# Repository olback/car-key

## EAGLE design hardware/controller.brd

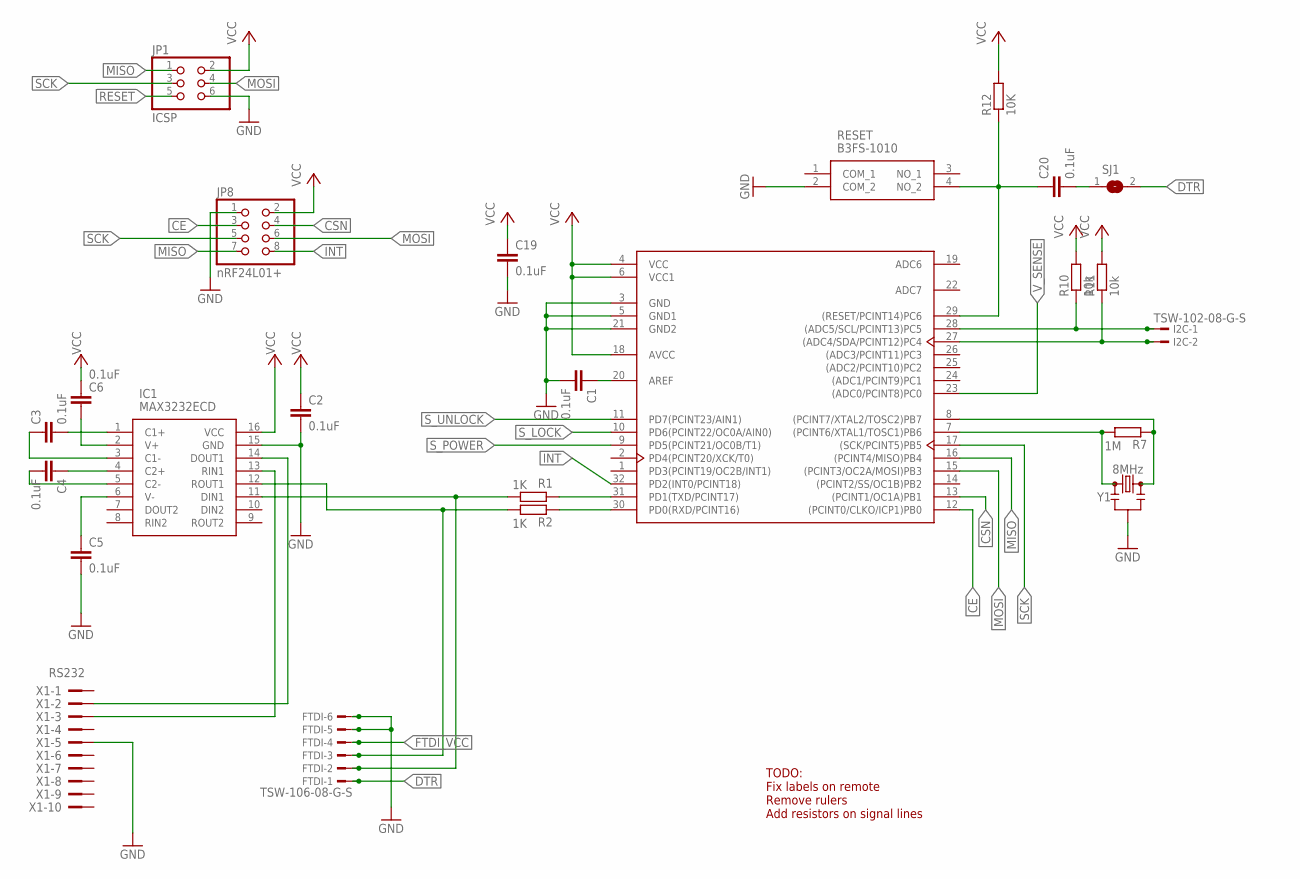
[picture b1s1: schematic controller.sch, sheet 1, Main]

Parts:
C1, C2, C3, C4, C5, C6, C19, C20: 0.1uF; C0805
FTDI: TSW-106-08-G-S; TSW-106-XX-G-S
I2C: TSW-102-08-G-S; TSW-102-XX-G-S
IC1: MAX3232ECD; SOIC127P600X175-16N
JP1: ICSP; 2X03
JP8: nRF24L01+; 2X04
R1, R2: 1K; R0805
R7: 1M; R0805
R10, R11: 10k; R0805
R12: 10K; R0805
RESET: B3FS-1010; B3FS-1000P
SJ1: SJ
U2: ATMEGA328P-AU; TQFP-32
X1: RS232; PAK100/2500-10
Y1: 8MHz; RESONATOR-SMD-3.2X1.3

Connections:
CE: JP8.3, U2.12 ((PCINT0/CLKO/ICP1)PB0); also elsewhere on the board
CSN: JP8.4, U2.13 ((PCINT1/OC1A)PB1); also elsewhere on the board
DTR: FTDI.1, SJ1.2
FTDI_VCC: FTDI.4; also elsewhere on the board
GND: C1.2, C2.2, C5.2, C19.2, FTDI.5, FTDI.6, IC1.15 (GND), JP1.6, JP8.1, RESET.2 (COM_2), U2.3 (GND), U2.5 (GND1), U2.21 (GND2), X1.5, Y1.2; also elsewhere on the board
INT: JP8.8, U2.32 (PD2(INT0/PCINT18)); also elsewhere on the board
MISO: JP1.1, JP8.7, U2.16 ((PCINT4/MISO)PB4); also elsewhere on the board
MOSI: JP1.4, JP8.6, U2.15 ((PCINT3/OC2A/MOSI)PB3); also elsewhere on the board
unnamed: C1.1, U2.20 (AREF)
unnamed: R7.2, U2.7 ((PCINT6/XTAL1/TOSC1)PB6), Y1.1
unnamed: R7.1, U2.8 ((PCINT7/XTAL2/TOSC2)PB7), Y1.3
unnamed: R1.1, U2.31 (PD1(TXD/PCINT17))
unnamed: R2.1, U2.30 (PD0(RXD/PCINT16))
unnamed: C5.1, IC1.6 (V-)
unnamed: C3.2, IC1.1 (C1+)
unnamed: C4.2, IC1.5 (C2-)
unnamed: C3.1, IC1.3 (C1-)
unnamed: C4.1, IC1.4 (C2+)
unnamed: C6.1, IC1.2 (V+)
unnamed: IC1.13 (RIN1), X1.3
unnamed: IC1.14 (DOUT1), X1.2
unnamed: C20.2, SJ1.1
RESET: C20.1, JP1.5, R12.1, RESET.4 (NO_2), U2.29 ((RESET/PCINT14)PC6)
RX-I: FTDI.3, IC1.12 (ROUT1), R2.2
SCK: JP1.3, JP8.5, U2.17 ((SCK/PCINT5)PB5); also elsewhere on the board
SCL: I2C.1, R10.1, U2.28 ((ADC5/SCL/PCINT13)PC5)
SDA: I2C.2, R11.1, U2.27 ((ADC4/SDA/PCINT12)PC4)
S_LOCK: U2.10 (PD6(PCINT22/OC0A/AIN0)); also elsewhere on the board
S_POWER: U2.9 (PD5(PCINT21/OC0B/T1)); also elsewhere on the board
S_UNLOCK: U2.11 (PD7(PCINT23/AIN1)); also elsewhere on the board
TX-O: FTDI.2, IC1.11 (DIN1), R1.2
VCC: C2.1, C6.2, C19.1, IC1.16 (VCC), JP1.2, JP8.2, R10.2, R11.2, R12.2, U2.4 (VCC), U2.6 (VCC1), U2.18 (AVCC); also elsewhere on the board
V_SENSE: U2.23 ((ADC0/PCINT8)PC0); also elsewhere on the board

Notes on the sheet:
TODO: Fix labels on remote Remove rulers Add resistors on signal lines

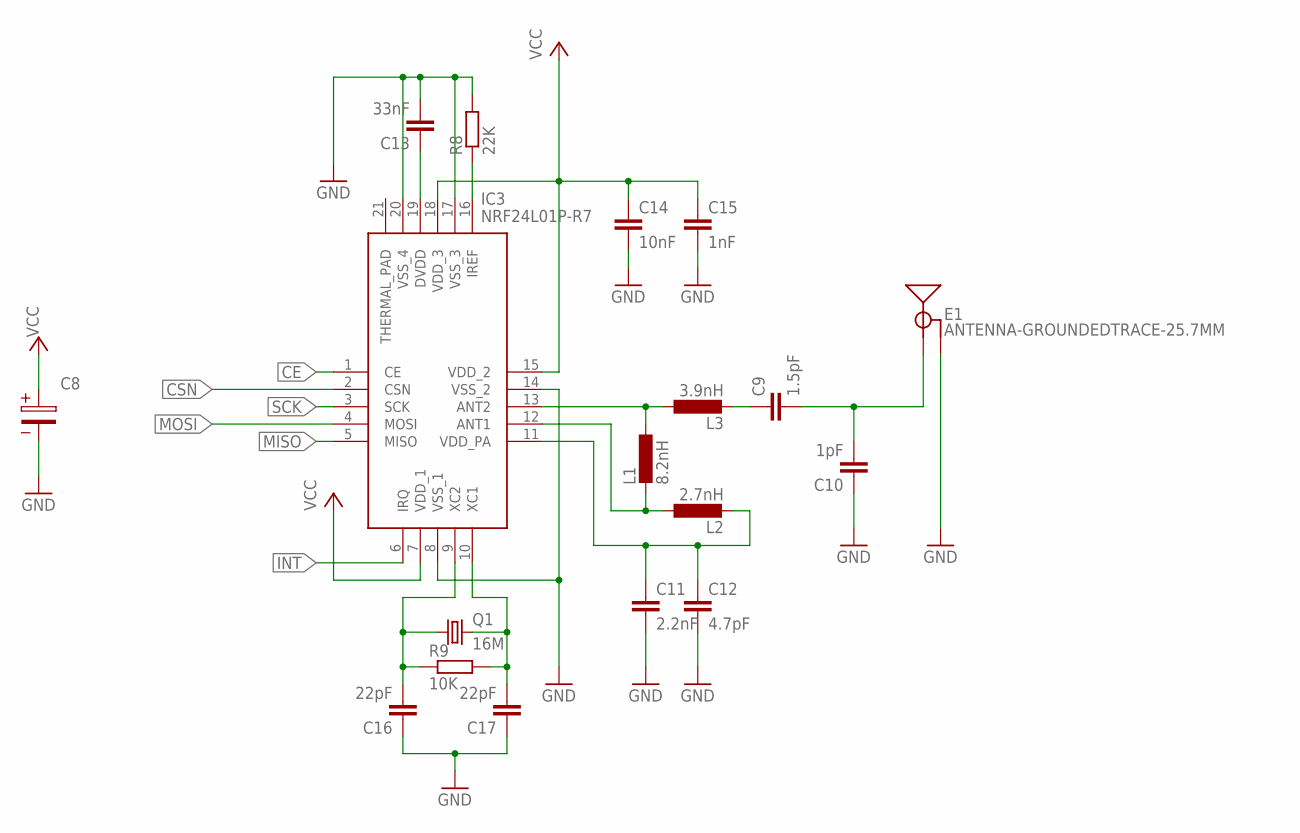
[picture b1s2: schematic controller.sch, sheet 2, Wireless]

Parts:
C8: WCAP-ASLI_8X6,5_865080149011; 4.2X1.9X2.8(BXCXA)
C9: 1.5pF; C0805
C10: 1pF; C0805
C11: 2.2nF; C0805
C12: 4.7pF; C0805
C13: 33nF; C0805
C14: 10nF; C0805
C15: 1nF; C0805
C16, C17: 22pF; C0805
E1: ANTENNA-GROUNDEDTRACE-25.7MM; TRACE_ANTENNA_2.4GHZ_25.7MM
IC3: NRF24L01P-R7; QFN50P400X400X95-21N
L1: 8.2nH; L2012C
L2: 2.7nH; L2012C
L3: 3.9nH; L2012C
Q1: 16M; HC49/S
R8: 22K; R0805
R9: 10K; R0805

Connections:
CE: IC3.1 (CE); also elsewhere on the board
CSN: IC3.2 (CSN); also elsewhere on the board
GND: C8.2, C10.1, C11.2, C12.2, C13.2, C14.2, C15.2, C16.1, C17.1, E1.GND, E1.GND2 (GND), IC3.8 (VSS_1), IC3.14 (VSS_2), IC3.17 (VSS_3), IC3.20 (VSS_4), R8.2; also elsewhere on the board
INT: IC3.6 (IRQ); also elsewhere on the board
MISO: IC3.5 (MISO); also elsewhere on the board
MOSI: IC3.4 (MOSI); also elsewhere on the board
unnamed: IC3.13 (ANT2), L1.1, L3.1
unnamed: IC3.12 (ANT1), L1.2, L2.1
unnamed: C11.1, C12.1, IC3.11 (VDD_PA), L2.2
unnamed: C9.1, L3.2
unnamed: C9.2, C10.2, E1.ANT (SIGNAL)
unnamed: C13.1, IC3.19 (DVDD)
unnamed: C16.2, IC3.9 (XC2), Q1.1, R9.1
unnamed: C17.2, IC3.10 (XC1), Q1.2, R9.2
unnamed: IC3.16 (IREF), R8.1
SCK: IC3.3 (SCK); also elsewhere on the board
VCC: C8.1, C14.1, C15.1, IC3.7 (VDD_1), IC3.15 (VDD_2), IC3.18 (VDD_3); also elsewhere on the board

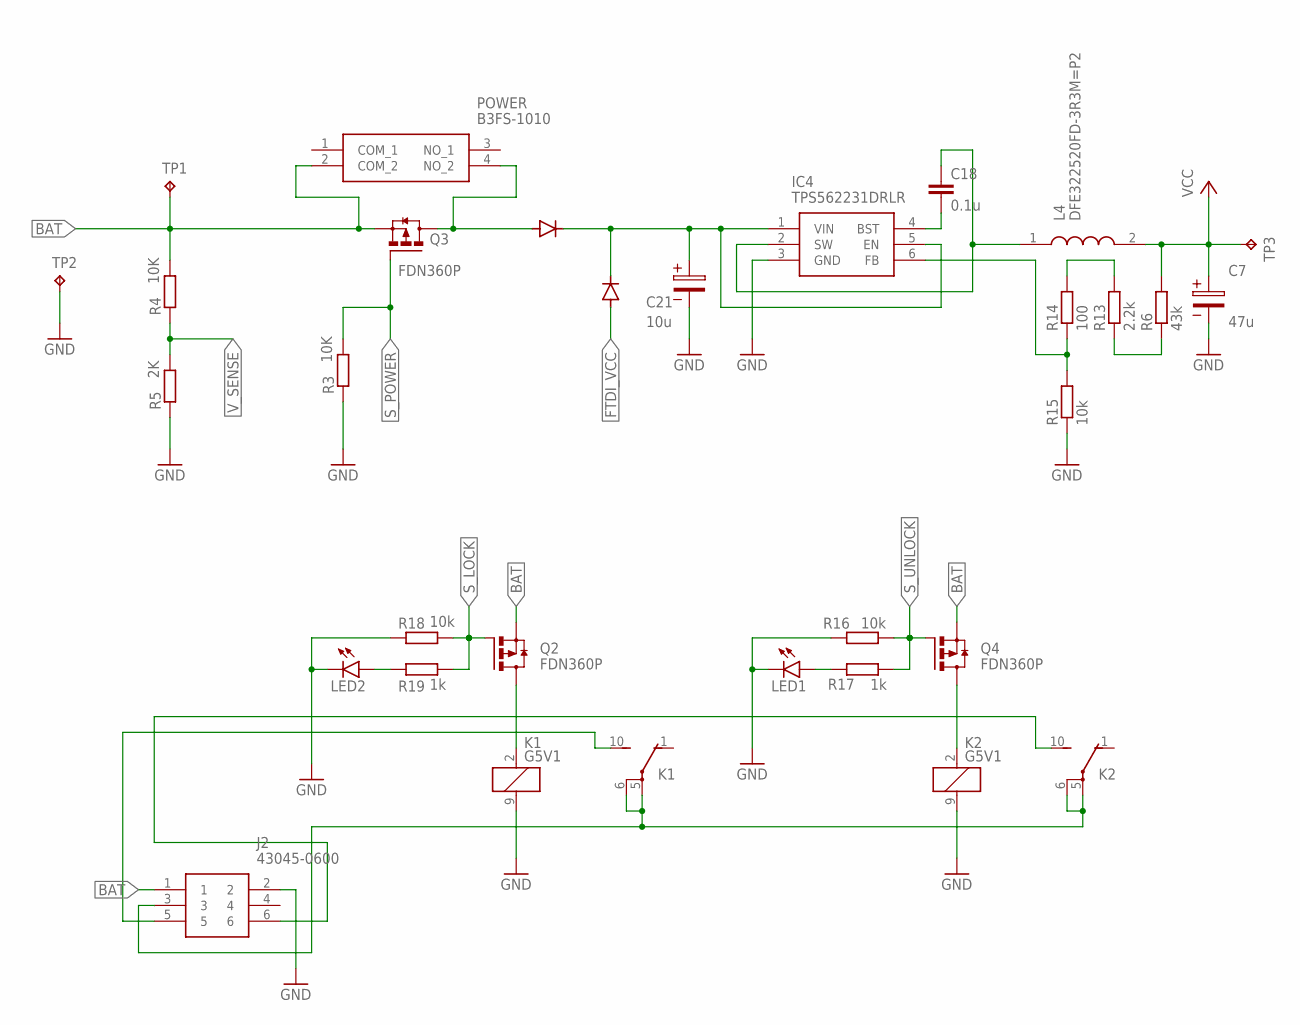
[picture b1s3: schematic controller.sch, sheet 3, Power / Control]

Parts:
C7: 47u; 2.6X1.6X1(BXCXA)
C18: 0.1u; C0805
C21: 10u; 2.6X1.6X1(BXCXA)
D1, D2: DIODE-SOD123; SOD123
IC4: TPS562231DRLR; SOTFL50P160X60-6N
J2: 43045-0600
K1, K2: G5V1
L4: DFE322520FD-3R3M=P2; INDC3225X200N
LED1, LED2: LEDCHIPLED_0805; CHIPLED_0805
POWER: B3FS-1010; B3FS-1000P
Q2, Q3, Q4: FDN360P; SUPER-SOT3
R3, R4: 10K; R0805
R5: 2K; R0805
R6: 43k; R0805
R13: 2.2k; R0805
R14: 100; R0805
R15, R16, R18: 10k; R0805
R17, R19: 1k; R0805
TP1, TP2, TP3: TPB1,27; B1,27

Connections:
BAT: J2.1, POWER.2 (COM_2), Q2.2 (S), Q3.2 (S), Q4.2 (S), R4.2, TP1.TP
E_LOCK: J2.5, K1.10 (S)
E_UNLOCK: J2.6, K2.10 (S)
FTDI_VCC: D1.A; also elsewhere on the board
GND: C7.2, C21.2, IC4.3 (GND), J2.2, K1.9 (2), K2.9 (2), LED1.C, LED2.C, R3.1, R5.1, R15.1, R16.2, R18.1, TP2.TP; also elsewhere on the board
unnamed: C18.1, IC4.2 (SW), L4.1
unnamed: C18.2, IC4.4 (BST)
unnamed: R13.2, R14.2
unnamed: C21.1, D1.C, D2.C, IC4.1 (VIN), IC4.5 (EN)
unnamed: J2.3, K1.5, K1.6, K2.5, K2.6
unnamed: R6.1, R13.1
unnamed: IC4.6 (FB), R14.1, R15.2
unnamed: D2.A, POWER.4 (NO_2), Q3.3 (D)
unnamed: K1.2 (1), Q2.3 (D)
unnamed: K2.2 (1), Q4.3 (D)
unnamed: LED1.A, R17.2
unnamed: LED2.A, R19.1
S_LOCK: Q2.1 (G), R18.2, R19.2; also elsewhere on the board
S_POWER: Q3.1 (G), R3.2; also elsewhere on the board
S_UNLOCK: Q4.1 (G), R16.1, R17.1; also elsewhere on the board
VCC: C7.1, L4.2, R6.2, TP3.TP; also elsewhere on the board
V_SENSE: R4.1, R5.2; also elsewhere on the board

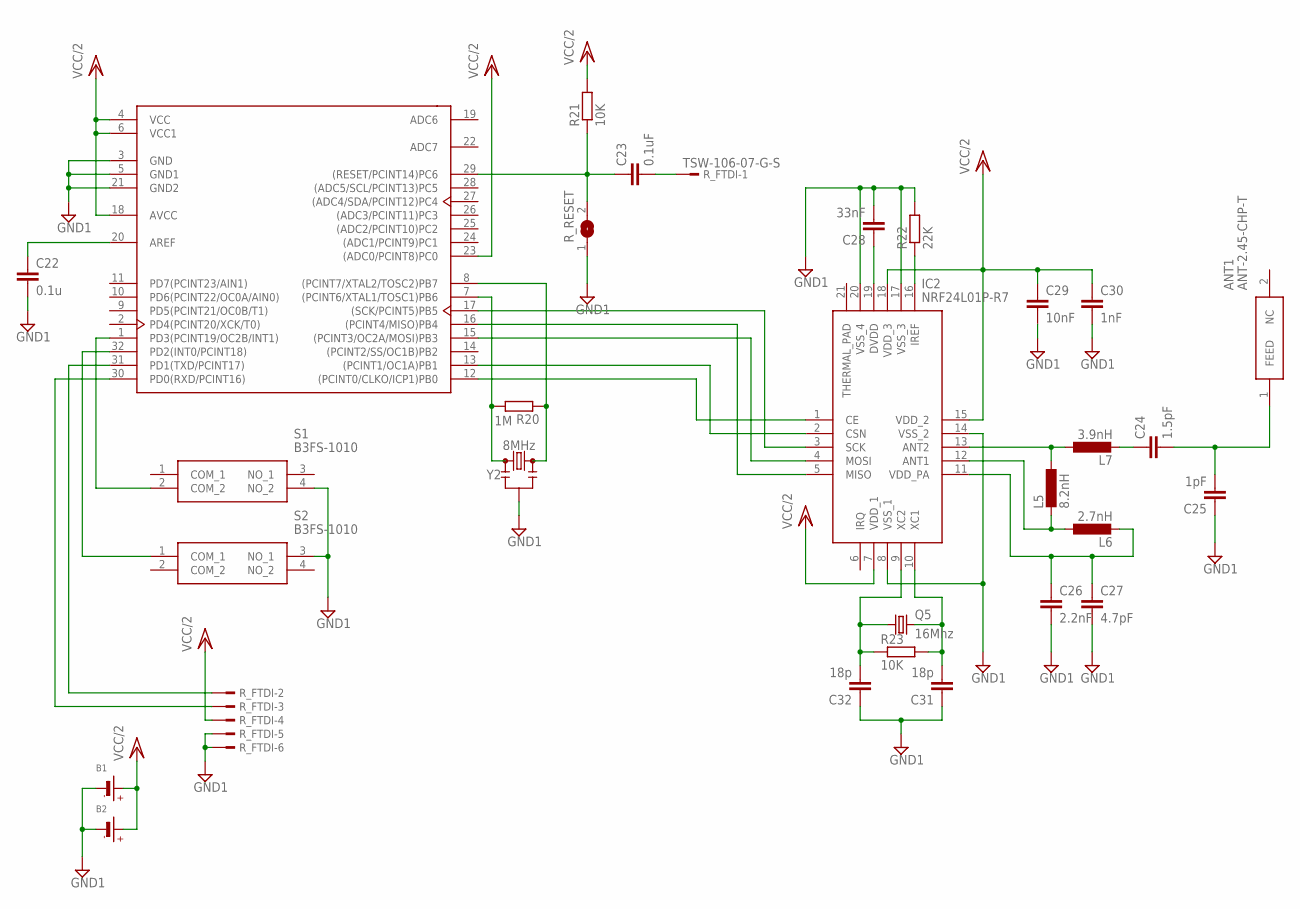
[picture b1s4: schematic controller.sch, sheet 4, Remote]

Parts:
ANT1: ANT-2.45-CHP-T
B1, B2: BATTERYCR2032_BAT-HLD-001; CR2032_SMT_BAT-HLD-001
C22: 0.1u; C0805
C23: 0.1uF; C0805
C24: 1.5pF; C0805
C25: 1pF; C0805
C26: 2.2nF; C0805
C27: 4.7pF; C0805
C28: 33nF; C0805
C29: 10nF; C0805
C30: 1nF; C0805
C31, C32: 18p; C0805
IC2: NRF24L01P-R7; QFN50P400X400X95-21N
L5: 8.2nH; L2012C
L6: 2.7nH; L2012C
L7: 3.9nH; L2012C
Q5: 16Mhz; HC49UP
R20: 1M; R0805
R21, R23: 10K; R0805
R22: 22K; R0805
R_FTDI: TSW-106-07-G-S; TSW-106-XX-G-S
R_RESET: SJ
S1, S2: B3FS-1010; B3FS-1000P
U1: ATMEGA328P-AU; TQFP-32
Y2: 8MHz; RESONATOR-SMD-3.2X1.3

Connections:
GND1: B1.-, B2.-, C22.2, C25.1, C26.2, C27.2, C28.2, C29.2, C30.2, C31.1, C32.1, IC2.8 (VSS_1), IC2.14 (VSS_2), IC2.17 (VSS_3), IC2.20 (VSS_4), R22.2, R_FTDI.5, R_FTDI.6, R_RESET.1, S1.4 (NO_2), S2.3 (NO_1), U1.3 (GND), U1.5 (GND1), U1.21 (GND2), Y2.2
unnamed: R20.2, U1.7 ((PCINT6/XTAL1/TOSC1)PB6), Y2.1
unnamed: R20.1, U1.8 ((PCINT7/XTAL2/TOSC2)PB7), Y2.3
unnamed: C22.1, U1.20 (AREF)
unnamed: S1.2 (COM_2), U1.1 (PD3(PCINT19/OC2B/INT1))
unnamed: S2.1 (COM_1), U1.32 (PD2(INT0/PCINT18))
unnamed: C23.2, R_FTDI.1
unnamed: C23.1, R21.1, R_RESET.2, U1.29 ((RESET/PCINT14)PC6)
unnamed: IC2.13 (ANT2), L5.1, L7.1
unnamed: R_FTDI.2, U1.31 (PD1(TXD/PCINT17))
unnamed: R_FTDI.3, U1.30 (PD0(RXD/PCINT16))
unnamed: IC2.12 (ANT1), L5.2, L6.1
unnamed: C26.1, C27.1, IC2.11 (VDD_PA), L6.2
unnamed: C24.1, L7.2
unnamed: ANT1.1 (FEED), C24.2, C25.2
unnamed: C32.2, IC2.9 (XC2), Q5.1, R23.1
unnamed: C31.2, IC2.10 (XC1), Q5.2, R23.2
unnamed: IC2.16 (IREF), R22.1
unnamed: C28.1, IC2.19 (DVDD)
unnamed: IC2.3 (SCK), U1.17 ((SCK/PCINT5)PB5)
unnamed: IC2.5 (MISO), U1.16 ((PCINT4/MISO)PB4)
unnamed: IC2.4 (MOSI), U1.15 ((PCINT3/OC2A/MOSI)PB3)
unnamed: IC2.2 (CSN), U1.13 ((PCINT1/OC1A)PB1)
unnamed: IC2.1 (CE), U1.12 ((PCINT0/CLKO/ICP1)PB0)
VCC/2: B1.+$1 (+), B1.+$2 (+), B2.+$1 (+), B2.+$2 (+), C29.1, C30.1, IC2.7 (VDD_1), IC2.15 (VDD_2), IC2.18 (VDD_3), R21.2, R_FTDI.4, U1.4 (VCC), U1.6 (VCC1), U1.18 (AVCC), U1.23 ((ADC0/PCINT8)PC0)

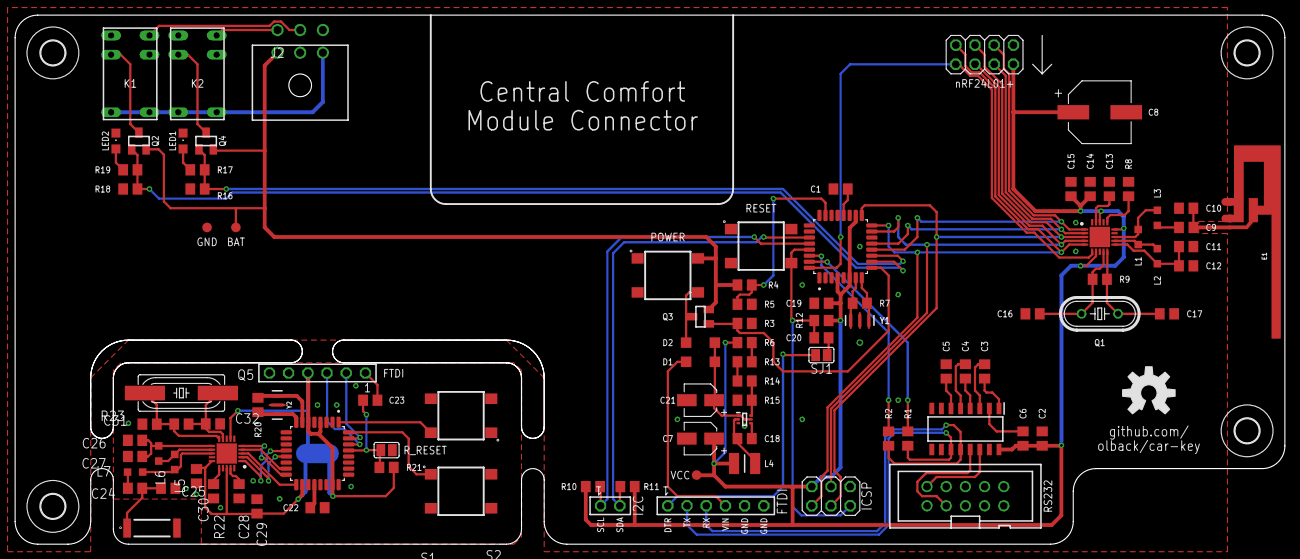
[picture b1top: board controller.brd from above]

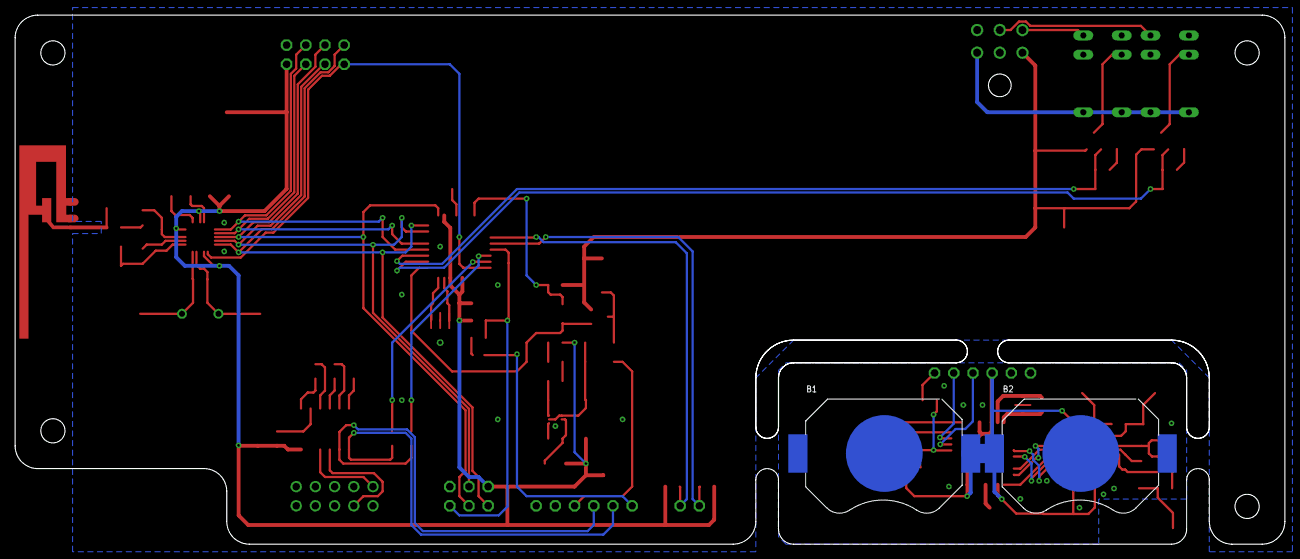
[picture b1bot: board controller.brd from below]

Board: 2 copper layers, 168.0 x 70.0 mm, 106 parts (2 on the bottom side), 82 nets.

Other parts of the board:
U$1, U$2, U$3, U$4: 3,2
U$5: OSHW-LOGO-L

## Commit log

2019-10-28 Major additions
2019-10-30 progress
2019-11-05 move psu, labels
2019-11-07 restructure + initial software drafts
2019-11-07 added base class header plus some
2019-11-09 lots of stuff
2019-11-10 start remote
2019-11-10 use 3x2 instead of 5x1
2019-11-10 move
2019-11-12 added some test stuff
2019-11-17 remote
2019-11-19 test stuff
2019-11-20 dunno

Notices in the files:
parts and their libraries:
SparkFun-Clocks: Licensing: Creative Commons ShareAlike 4.0 International - https://creativecommons.org/licenses/by-sa/4.0
Wurth_Elektronik_Passive_Capacitors_rev1: Copyright: Würth Elektronik
